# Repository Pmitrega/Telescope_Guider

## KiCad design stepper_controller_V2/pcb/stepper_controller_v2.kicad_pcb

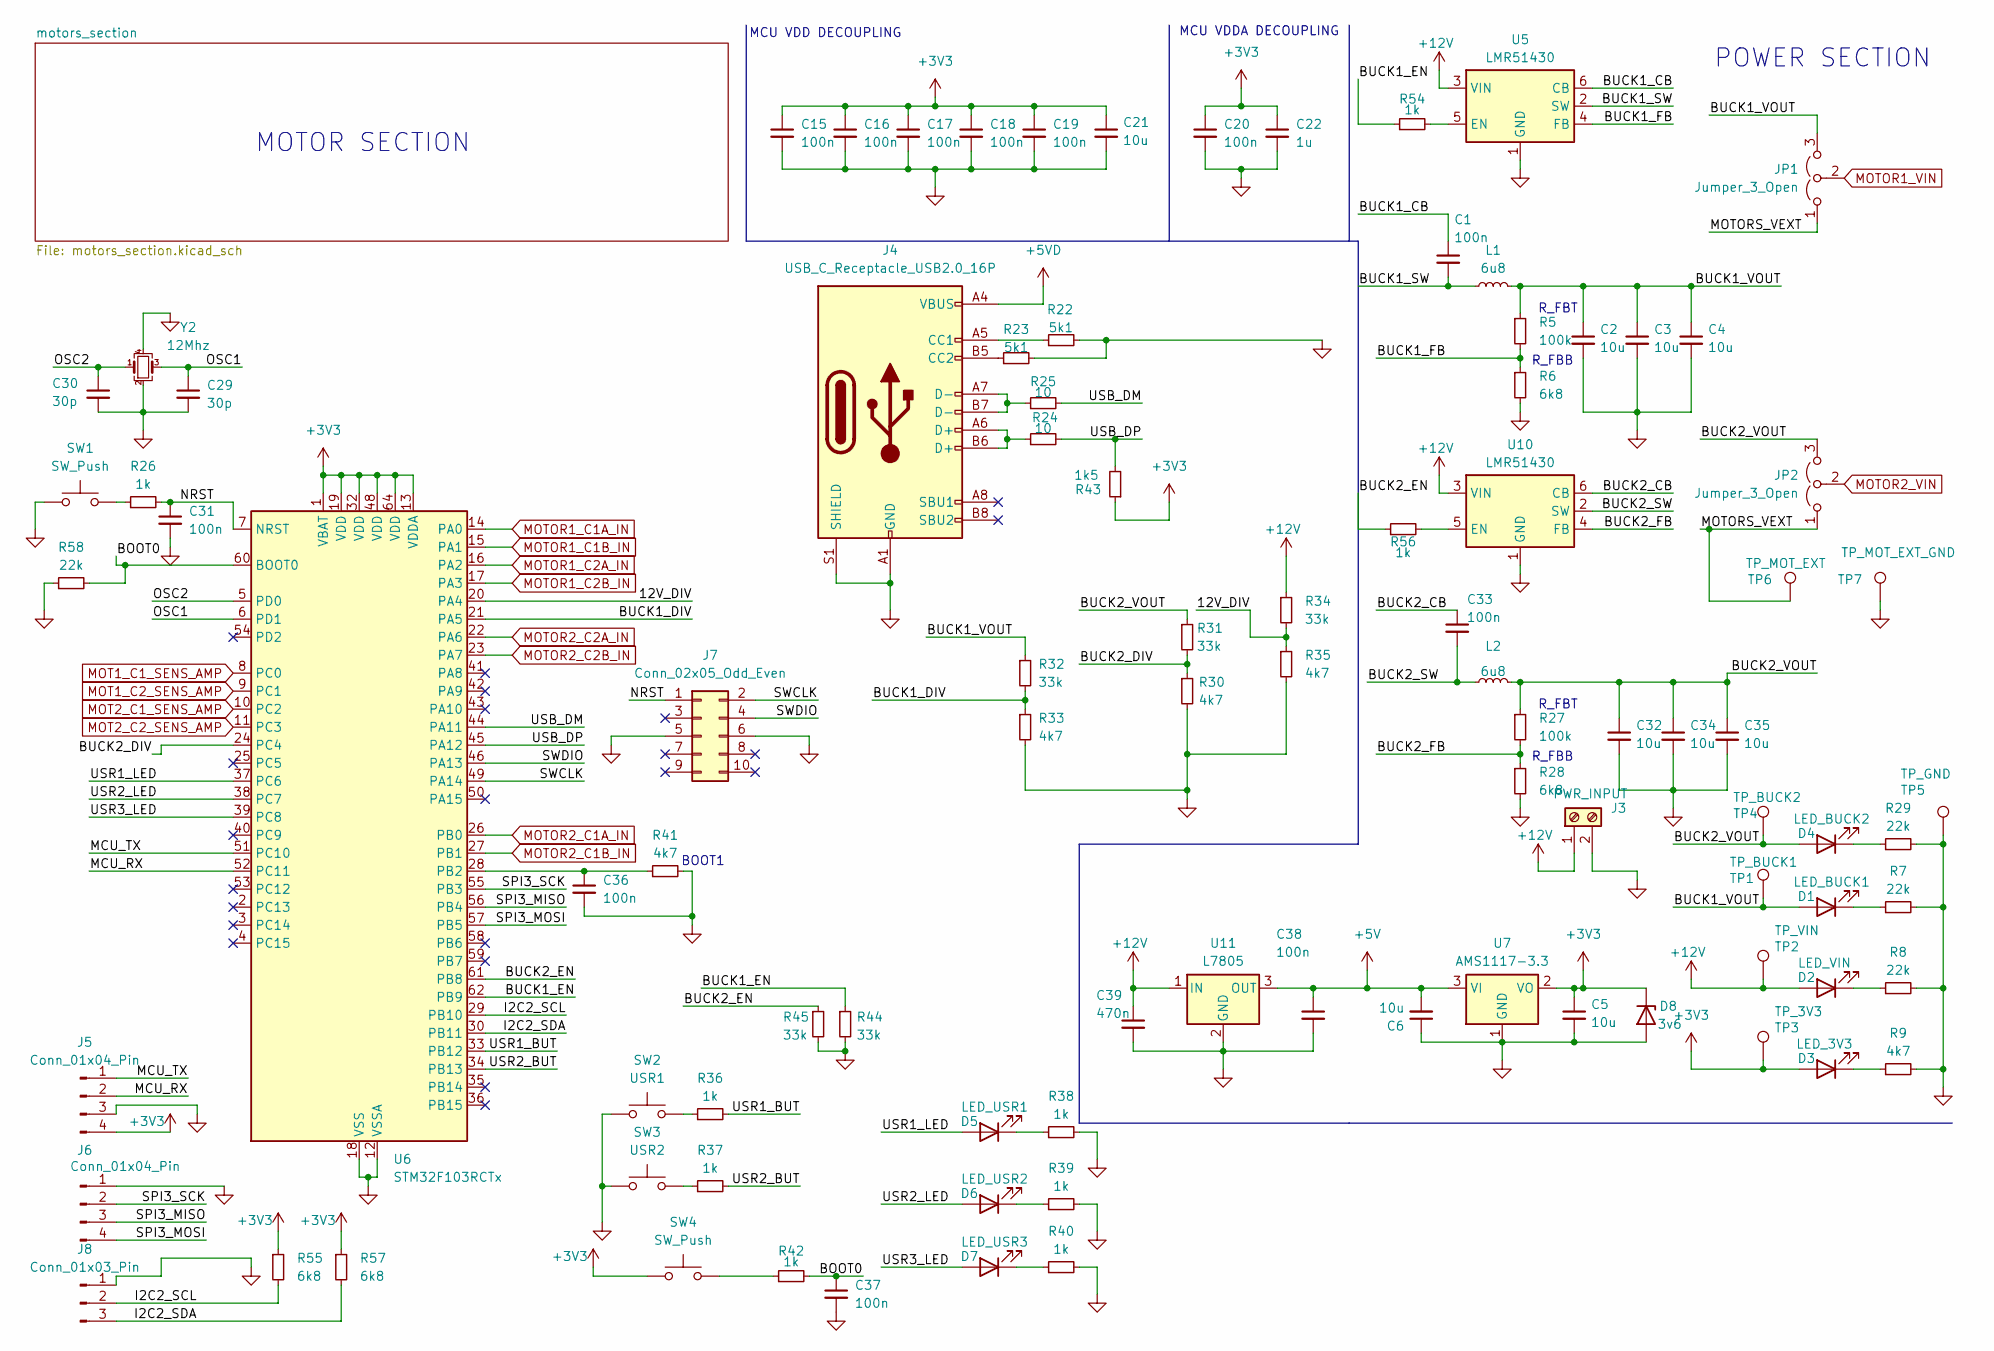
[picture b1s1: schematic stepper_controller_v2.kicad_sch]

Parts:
C1, C15, C16, C17, C18, C19, C20, C31, C33, C36, C37, C38: 100n; C_0603_1608Metric; LCSC C14663
C2, C3, C4, C5, C6, C21, C32, C34, C35: 10u; C_0805_2012Metric; LCSC C15850
C22: 1u; C_0603_1608Metric; LCSC C15849
C29, C30: 30p; C_0603_1608Metric; LCSC C1658
C39: 470n; C_0603_1608Metric; LCSC C1623
D1: LED_BUCK1; LED_0603_1608Metric; LCSC C2286
D2: LED_VIN; LED_0603_1608Metric; LCSC C2286
D3: LED_3V3; LED_0603_1608Metric; LCSC C2286
D4: LED_BUCK2; LED_0603_1608Metric; LCSC C2286
D5: LED_USR1; LED_0603_1608Metric; LCSC C2286
D6: LED_USR2; LED_0603_1608Metric; LCSC C2286
D7: LED_USR3; LED_0603_1608Metric; LCSC C2286
D8: 3v6; D_SOD-323; LCSC C12757
J3: PWR_INPUT; TerminalBlock_bornier-2_P5.08mm
J4: USB_C_Receptacle_USB2.0_16P; USB_C_Receptacle_GCT_USB4105-xx-A_16P_TopMnt_Horizontal; LCSC C2765186
J5, J6: Conn_01x04_Pin; PinHeader_1x04_P2.54mm_Vertical
J7: Conn_02x05_Odd_Even; IDC-Header_2x05_P2.54mm_Vertical
J8: Conn_01x03_Pin; PinHeader_1x03_P2.54mm_Vertical
JP1, JP2: Jumper_3_Open; SolderJumper-3_P1.3mm_Open_Pad1.0x1.5mm
L1, L2: 6u8; L_Changjiang_FNR8040S; LCSC C431374
R5, R27: 100k; R_0603_1608Metric; LCSC C25803
R6, R28, R55, R57: 6k8; R_0603_1608Metric; LCSC C23212
R7, R8, R29, R58: 22k; R_0603_1608Metric; LCSC C31850
R9, R30, R33, R35, R41: 4k7; R_0603_1608Metric; LCSC C23162
R22, R23: 5k1; R_0603_1608Metric; LCSC C23186
R24, R25: 10; R_0603_1608Metric; LCSC C22859
R26, R36, R37, R38, R39, R40, R42, R54, R56: 1k; R_0603_1608Metric; LCSC C21190
R31, R32, R34, R44, R45: 33k; R_0603_1608Metric; LCSC C4216
R43: 1k5; R_0603_1608Metric; LCSC C22843
SW1, SW4: SW_Push; stepper TACT_SWITCH; LCSC C720477
SW2: USR1; stepper TACT_SWITCH; LCSC C720477
SW3: USR2; stepper TACT_SWITCH; LCSC C720477
TP1: TP_BUCK1; TestPoint_Pad_D1.5mm
TP2: TP_VIN; TestPoint_Pad_D1.5mm
TP3: TP_3V3; TestPoint_Pad_D1.5mm
TP4: TP_BUCK2; TestPoint_Pad_D1.5mm
TP5: TP_GND; TestPoint_Pad_D1.5mm
TP6: TP_MOT_EXT; TestPoint_Pad_D1.5mm
TP7: TP_MOT_EXT_GND; TestPoint_Pad_D1.5mm
U5, U10: LMR51430; SOT-23-6; LCSC C5219261
U6: STM32F103RCTx; LQFP-64_10x10mm_P0.5mm; LCSC C8323
U7: AMS1117-3.3; SOT-223-3_TabPin2; LCSC C6186
U11: L7805; TO-252-2; LCSC C58069
Y2: 12Mhz; Crystal_SMD_3225-4Pin_3.2x2.5mm; LCSC C9002

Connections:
+3V3: C5.1, C15.1, C16.1, C17.1, C18.1, C19.1, C20.1, C21.1, C22.1, D3.2 (A), D8.1 (K), J5.4, R43.1, R55.1, R57.1, SW4.1, TP3.1, U6.1 (VBAT), U6.13 (VDDA), U6.19 (VDD), U6.32 (VDD), U6.48 (VDD), U6.64 (VDD), U7.2 (VO); also elsewhere on the board
+5V: C6.2, C38.1, U7.3 (VI), U11.3 (OUT)
+5VD: J4.A4 (VBUS), J4.A9 (VBUS), J4.B4 (VBUS), J4.B9 (VBUS)
+12V: C39.1, D2.2 (A), J3.1, R34.1, TP2.1, U5.3 (VIN), U10.3 (VIN), U11.1 (IN)
/12V_DIV: R34.2, R35.1, U6.20 (PA4)
/BOOT0: C37.1, R42.2, R58.2, U6.60 (BOOT0)
/BUCK1_CB: C1.1, U5.6 (CB)
/BUCK1_DIV: R32.2, R33.1, U6.21 (PA5)
/BUCK1_EN: R44.1, R54.1, U6.62 (PB9)
/BUCK1_FB: R5.2, R6.1, U5.4 (FB)
/BUCK1_SW: C1.2, L1.1, U5.2 (SW)
/BUCK1_VOUT: C2.1, C3.1, C4.1, D1.2 (A), JP1.3 (B), L1.2, R5.1, R32.1, TP1.1
/BUCK2_CB: C33.1, U10.6 (CB)
/BUCK2_DIV: R30.1, R31.2, U6.24 (PC4)
/BUCK2_EN: R45.1, R56.1, U6.61 (PB8)
/BUCK2_FB: R27.2, R28.1, U10.4 (FB)
/BUCK2_SW: C33.2, L2.1, U10.2 (SW)
/BUCK2_VOUT: C32.1, C34.1, C35.1, D4.2 (A), JP2.3 (B), L2.2, R27.1, R31.1, TP4.1
/I2C2_SCL: J8.2, R55.2, U6.29 (PB10)
/I2C2_SDA: J8.3, R57.2, U6.30 (PB11)
/MCU_RX: J5.2, U6.52 (PC11)
/MCU_TX: J5.1, U6.51 (PC10)
/MOTORS_VEXT: JP1.1 (A), JP2.1 (A), TP6.1
/NRST: C31.1, J7.1, R26.2, U6.7 (NRST)
/OSC1: C29.1, U6.6 (PD1), Y2.3
/OSC2: C30.1, U6.5 (PD0), Y2.1
/SPI3_MISO: J6.3, U6.56 (PB4)
/SPI3_MOSI: J6.4, U6.57 (PB5)
/SPI3_SCK: J6.2, U6.55 (PB3)
/SWCLK: J7.2, U6.49 (PA14)
/SWDIO: J7.4, U6.46 (PA13)
/USB_DM: R25.2, U6.44 (PA11)
/USB_DP: R24.2, R43.2, U6.45 (PA12)
/USR1_BUT: R36.2, U6.33 (PB12)
/USR1_LED: D5.2 (A), U6.37 (PC6)
/USR2_BUT: R37.2, U6.34 (PB13)
/USR2_LED: D6.2 (A), U6.38 (PC7)
/USR3_LED: D7.2 (A), U6.39 (PC8)
GND: C2.2, C3.2, C4.2, C5.2, C6.1, C15.2, C16.2, C17.2, C18.2, C19.2, C20.2, C21.2, C22.2, C29.2, C30.2, C31.2, C32.2, C34.2, C35.2, C36.2, C37.2, C38.2, C39.2, D8.2 (A), J3.2, J4.A1 (GND), J4.A12 (GND), J4.B1 (GND), J4.B12 (GND), J4.S1 (SHIELD), J5.3, J6.1, J7.5, J7.6, J8.1, R6.2, R7.2, R8.2, R9.2, R22.2, R23.2, R28.2, R29.2, R30.2, R33.2, R35.2, R38.2, R39.2, R40.2, R41.2, R44.2, R45.2, R58.1, SW1.1, SW2.1, SW3.1, TP5.1, TP7.1, U5.1 (GND), U6.12 (VSSA), U6.18 (VSS), U6.31 (VSS), U6.47 (VSS), U6.63 (VSS), U7.1 (GND), U10.1 (GND), U11.2 (GND), Y2.2, Y2.4; also elsewhere on the board
MOT1_C1_SENS_AMP: U6.8 (PC0); also elsewhere on the board
MOT1_C2_SENS_AMP: U6.9 (PC1); also elsewhere on the board
MOT2_C1_SENS_AMP: U6.10 (PC2); also elsewhere on the board
MOT2_C2_SENS_AMP: U6.11 (PC3); also elsewhere on the board
MOTOR1_C1A_IN: U6.14 (PA0); also elsewhere on the board
MOTOR1_C1B_IN: U6.15 (PA1); also elsewhere on the board
MOTOR1_C2A_IN: U6.16 (PA2); also elsewhere on the board
MOTOR1_C2B_IN: U6.17 (PA3); also elsewhere on the board
MOTOR1_VIN: JP1.2 (C); also elsewhere on the board
MOTOR2_C1A_IN: U6.26 (PB0); also elsewhere on the board
MOTOR2_C1B_IN: U6.27 (PB1); also elsewhere on the board
MOTOR2_C2A_IN: U6.22 (PA6); also elsewhere on the board
MOTOR2_C2B_IN: U6.23 (PA7); also elsewhere on the board
MOTOR2_VIN: JP2.2 (C); also elsewhere on the board
unnamed: D1.1 (K), R7.1
unnamed: D2.1 (K), R8.1
unnamed: D3.1 (K), R9.1
unnamed: D4.1 (K), R29.1
unnamed: D5.1 (K), R38.1
unnamed: D6.1 (K), R39.1
unnamed: D7.1 (K), R40.1
unnamed: J4.A5 (CC1), R22.1
unnamed: J4.B5 (CC2), R23.1
unnamed: J4.A6 (D+), J4.B6 (D+), R24.1
unnamed: J4.A7 (D-), J4.B7 (D-), R25.1
unnamed: R26.1, SW1.2
unnamed: R36.1, SW2.2
unnamed: R37.1, SW3.2
unnamed: R42.1, SW4.2
unnamed: R54.2, U5.5 (EN)
unnamed: C36.1, R41.1, U6.28 (PB2)
unnamed: R56.2, U10.5 (EN)

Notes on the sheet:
R_FBT
MOTOR SECTION
POWER SECTION
MCU VDD DECOUPLING
R_FBB
BOOT1
MCU VDDA DECOUPLING

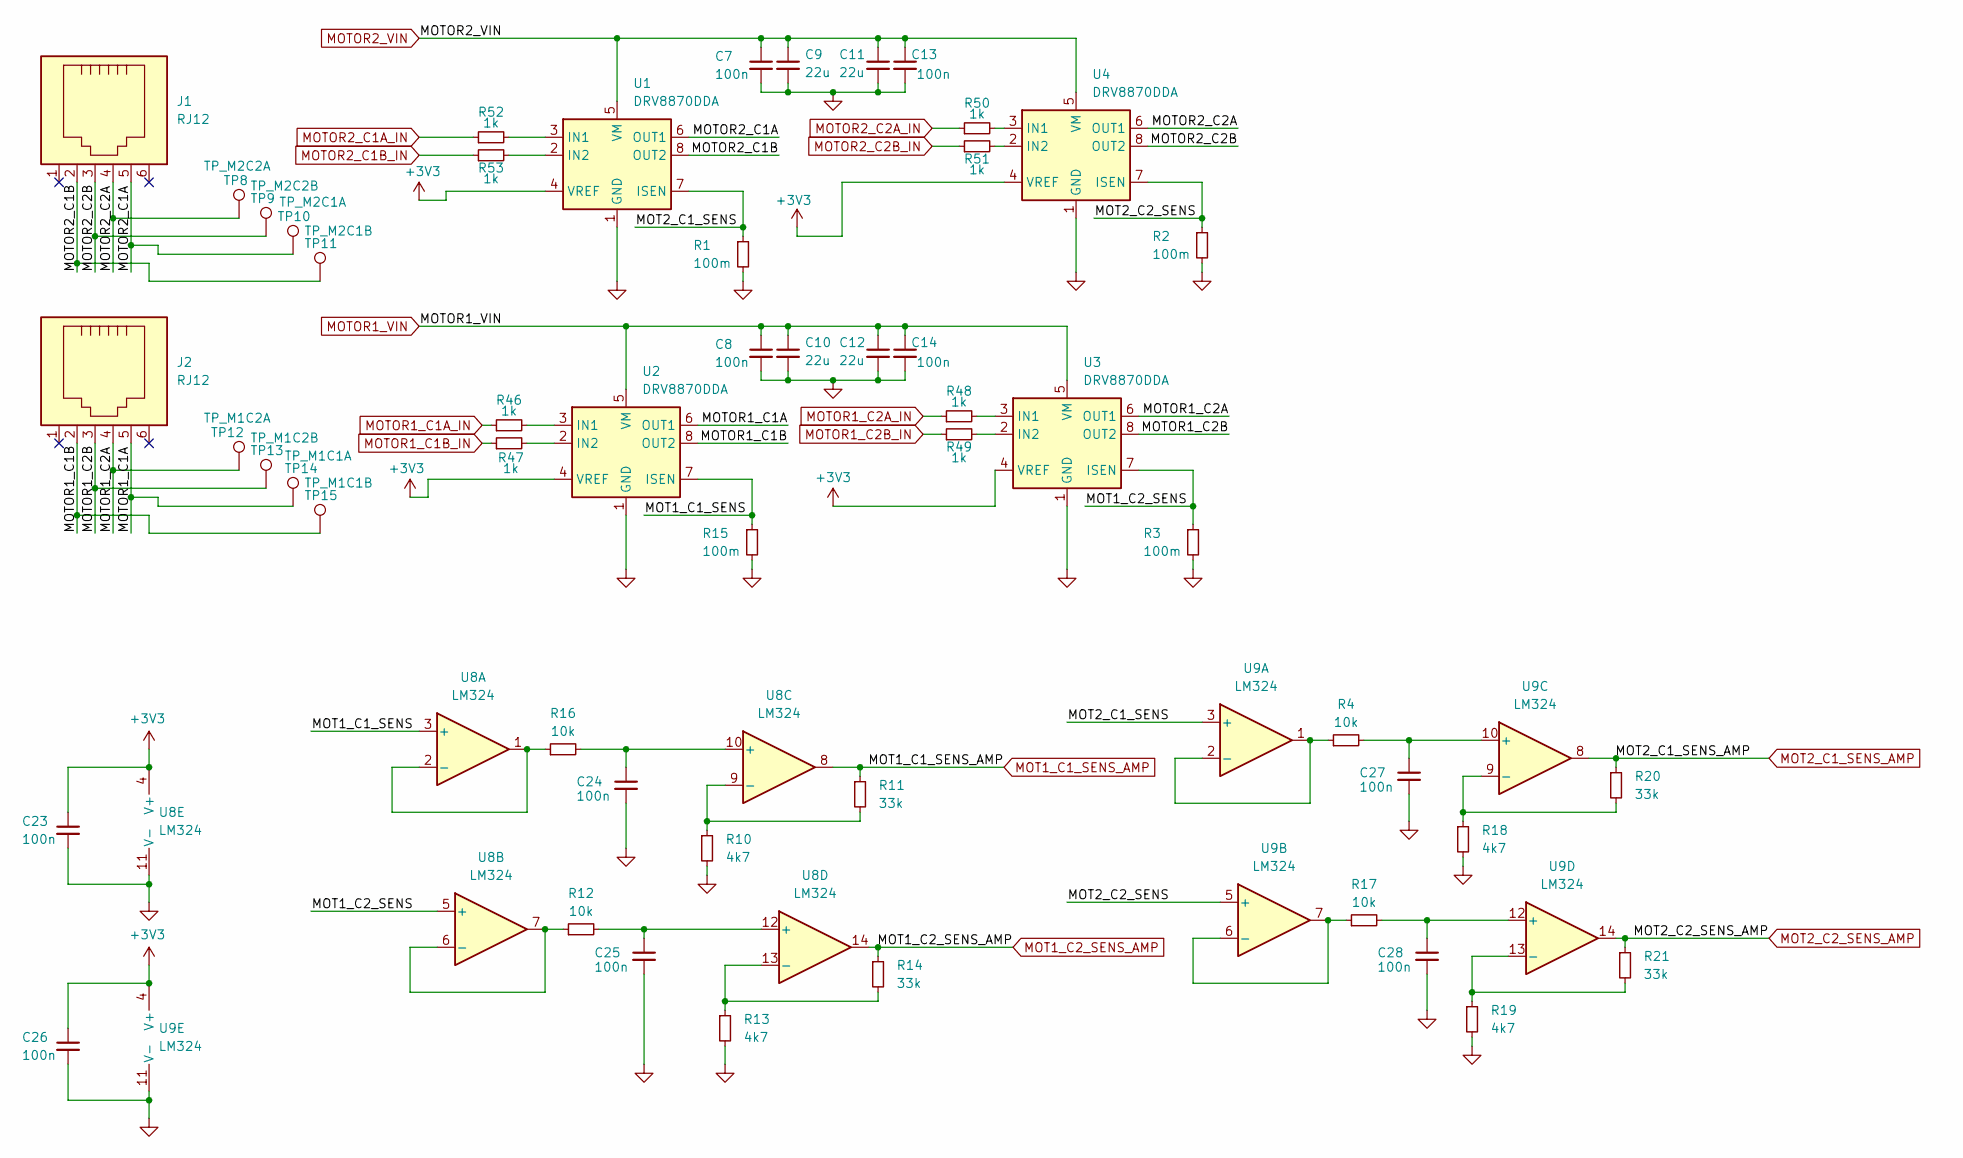
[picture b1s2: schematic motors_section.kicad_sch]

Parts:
C7, C8, C13, C14, C23, C24, C25, C26, C27, C28: 100n; C_0603_1608Metric; LCSC C14663
C9, C10, C11, C12: 22u; L_1210_3225Metric; LCSC C12891
J1, J2: RJ12; stepper ST4
R1, R2, R3, R15: 100m; R_0603_1608Metric; LCSC C111027
R4, R12, R16, R17: 10k; R_0603_1608Metric; LCSC C25804
R10, R13, R18, R19: 4k7; R_0603_1608Metric; LCSC C23162
R11, R14, R20, R21: 33k; R_0603_1608Metric; LCSC C4216
R46, R47, R48, R49, R50, R51, R52, R53: 1k; R_0603_1608Metric; LCSC C21190
TP8: TP_M2C2A; TestPoint_Pad_D1.0mm
TP9: TP_M2C2B; TestPoint_Pad_D1.0mm
TP10: TP_M2C1A; TestPoint_Pad_D1.0mm
TP11: TP_M2C1B; TestPoint_Pad_D1.0mm
TP12: TP_M1C2A; TestPoint_Pad_D1.0mm
TP13: TP_M1C2B; TestPoint_Pad_D1.0mm
TP14: TP_M1C1A; TestPoint_Pad_D1.0mm
TP15: TP_M1C1B; TestPoint_Pad_D1.0mm
U1, U2, U3, U4: DRV8870DDA; Texas_HTSOP-8-1EP_3.9x4.9mm_P1.27mm_EP2.95x4.9mm_Mask2.4x3.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; LCSC C86590
U8, U9: LM324; SOIC-14_3.9x8.7mm_P1.27mm; LCSC C71035

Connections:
+3V3: C23.1, C26.1, U1.4 (VREF), U2.4 (VREF), U3.4 (VREF), U4.4 (VREF), U8.4 (V+), U9.4 (V+); also elsewhere on the board
/motors_section/MOT1_C1_SENS: R15.1, U2.7 (ISEN), U8.3 (+)
/motors_section/MOT1_C2_SENS: R3.1, U3.7 (ISEN), U8.5 (+)
/motors_section/MOT2_C1_SENS: R1.1, U1.7 (ISEN), U9.3 (+)
/motors_section/MOT2_C2_SENS: R2.1, U4.7 (ISEN), U9.5 (+)
/motors_section/MOTOR1_C1A: J2.5, TP14.1, U2.6 (OUT1)
/motors_section/MOTOR1_C1B: J2.2, TP15.1, U2.8 (OUT2)
/motors_section/MOTOR1_C2A: J2.4, TP12.1, U3.6 (OUT1)
/motors_section/MOTOR1_C2B: J2.3, TP13.1, U3.8 (OUT2)
/motors_section/MOTOR2_C1A: J1.5, TP10.1, U1.6 (OUT1)
/motors_section/MOTOR2_C1B: J1.2, TP11.1, U1.8 (OUT2)
/motors_section/MOTOR2_C2A: J1.4, TP8.1, U4.6 (OUT1)
/motors_section/MOTOR2_C2B: J1.3, TP9.1, U4.8 (OUT2)
GND: C7.2, C8.2, C9.2, C10.2, C11.2, C12.2, C13.2, C14.2, C23.2, C24.2, C25.2, C26.2, C27.2, C28.2, R1.2, R2.2, R3.2, R10.2, R13.2, R15.2, R18.2, R19.2, U1.1 (GND), U1.9 (GND), U2.1 (GND), U2.9 (GND), U3.1 (GND), U3.9 (GND), U4.1 (GND), U4.9 (GND), U8.11 (V-), U9.11 (V-); also elsewhere on the board
MOT1_C1_SENS_AMP: R11.1, U8.8; also elsewhere on the board
MOT1_C2_SENS_AMP: R14.1, U8.14; also elsewhere on the board
MOT2_C1_SENS_AMP: R20.1, U9.8; also elsewhere on the board
MOT2_C2_SENS_AMP: R21.1, U9.14; also elsewhere on the board
MOTOR1_C1A_IN: R46.1; also elsewhere on the board
MOTOR1_C1B_IN: R47.1; also elsewhere on the board
MOTOR1_C2A_IN: R48.1; also elsewhere on the board
MOTOR1_C2B_IN: R49.1; also elsewhere on the board
MOTOR1_VIN: C8.1, C10.1, C12.1, C14.1, U2.5 (VM), U3.5 (VM); also elsewhere on the board
MOTOR2_C1A_IN: R52.1; also elsewhere on the board
MOTOR2_C1B_IN: R53.1; also elsewhere on the board
MOTOR2_C2A_IN: R50.1; also elsewhere on the board
MOTOR2_C2B_IN: R51.1; also elsewhere on the board
MOTOR2_VIN: C7.1, C9.1, C11.1, C13.1, U1.5 (VM), U4.5 (VM); also elsewhere on the board
unnamed: R52.2, U1.3 (IN1)
unnamed: R53.2, U1.2 (IN2)
unnamed: R46.2, U2.3 (IN1)
unnamed: R47.2, U2.2 (IN2)
unnamed: R48.2, U3.3 (IN1)
unnamed: R49.2, U3.2 (IN2)
unnamed: R50.2, U4.3 (IN1)
unnamed: R51.2, U4.2 (IN2)
unnamed: R16.1, U8.1, U8.2 (-)
unnamed: R12.1, U8.6 (-), U8.7
unnamed: C24.1, R16.2, U8.10 (+)
unnamed: R10.1, R11.2, U8.9 (-)
unnamed: C25.1, R12.2, U8.12 (+)
unnamed: R13.1, R14.2, U8.13 (-)
unnamed: R4.1, U9.1, U9.2 (-)
unnamed: R17.1, U9.6 (-), U9.7
unnamed: C27.1, R4.2, U9.10 (+)
unnamed: R18.1, R20.2, U9.9 (-)
unnamed: C28.1, R17.2, U9.12 (+)
unnamed: R19.1, R21.2, U9.13 (-)

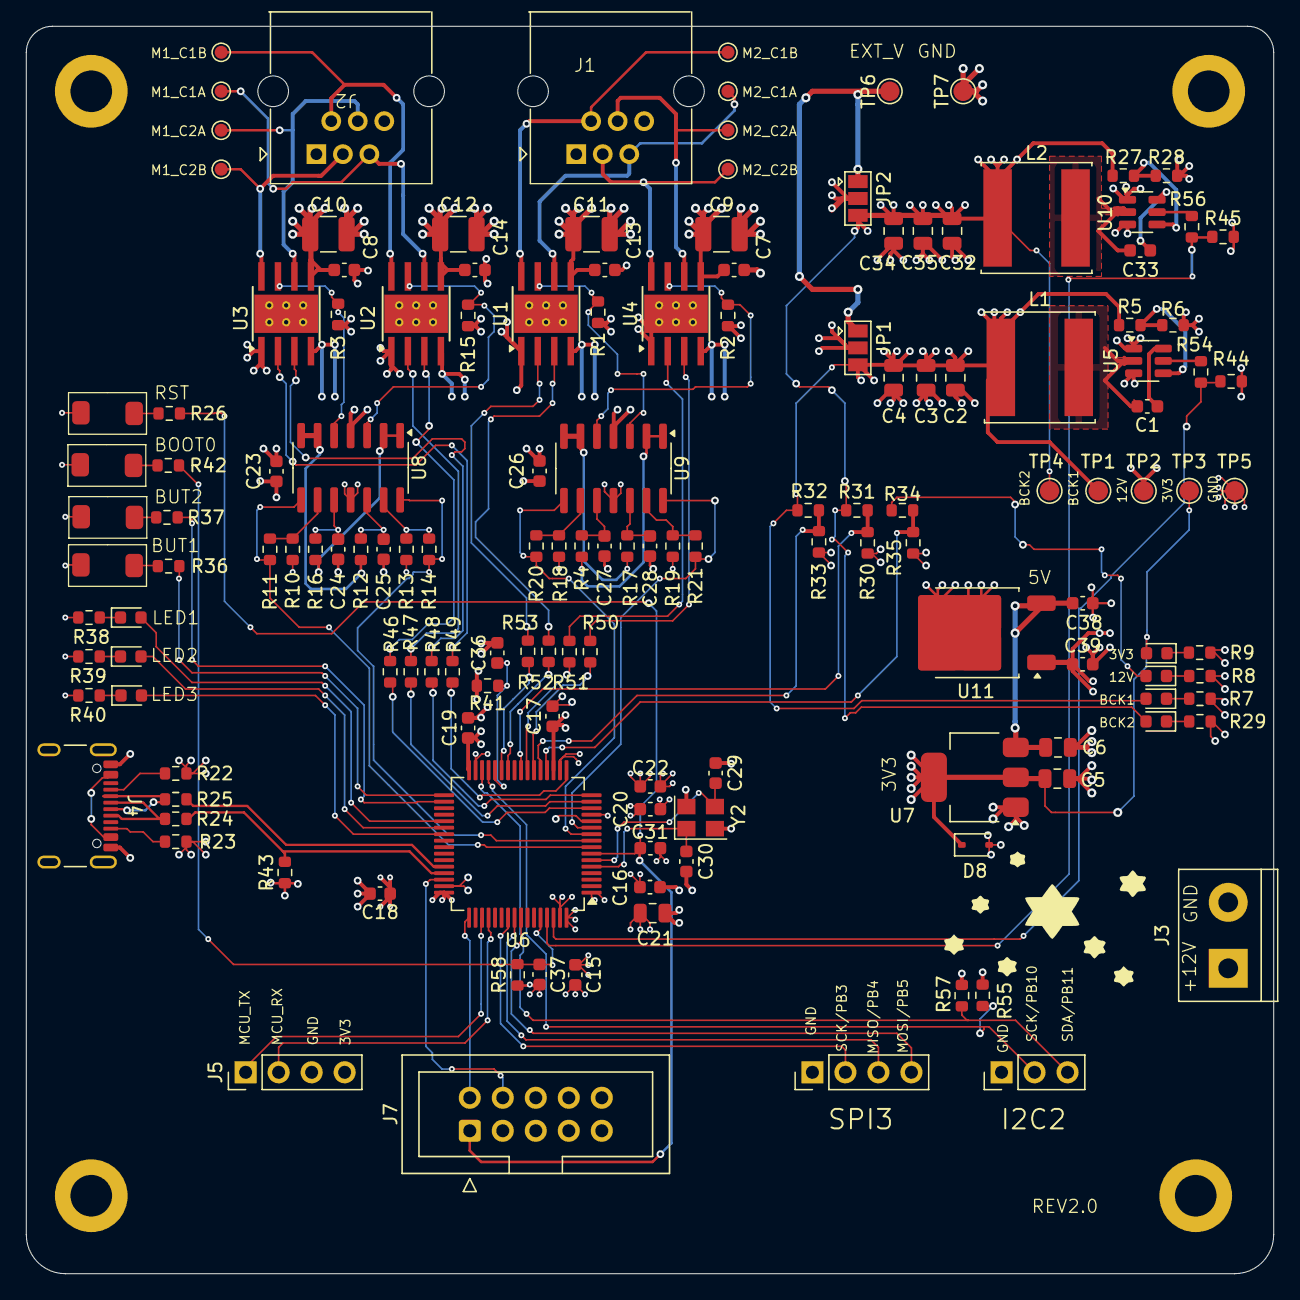
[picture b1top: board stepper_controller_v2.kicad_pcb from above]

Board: 4 copper layers, 96.0 x 96.0 mm, 148 parts (0 on the bottom side), 103 nets.

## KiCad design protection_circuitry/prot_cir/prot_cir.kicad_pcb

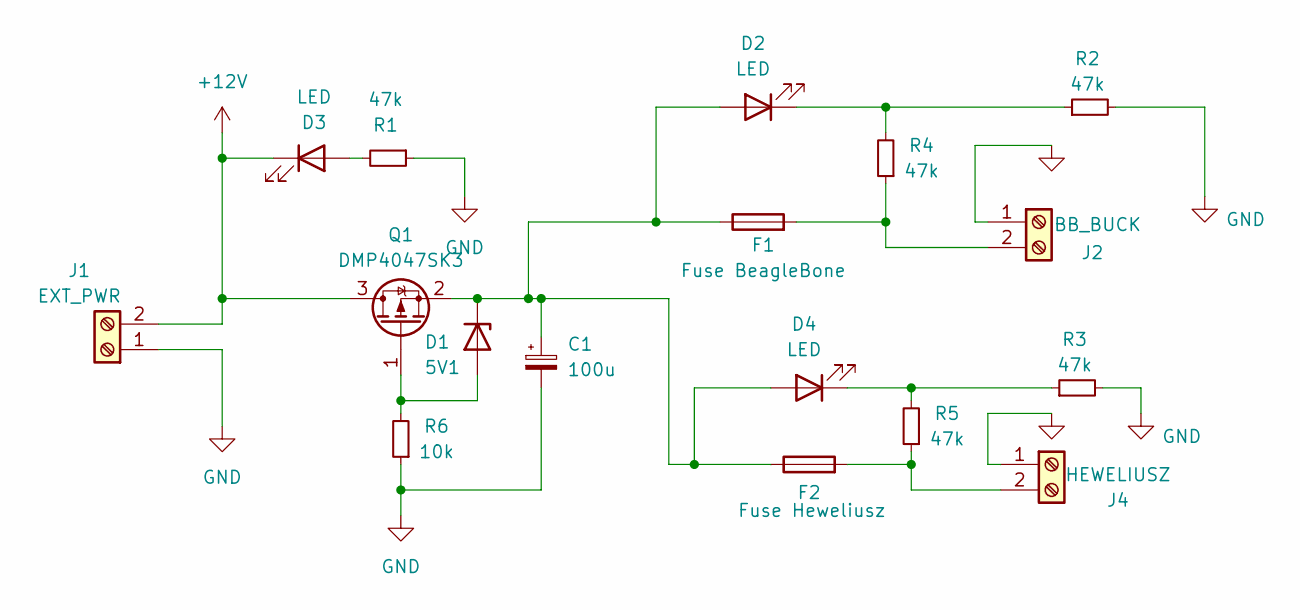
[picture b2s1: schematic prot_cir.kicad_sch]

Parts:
C1: 100u; CP_Radial_D6.3mm_P2.50mm
D1: 5V1; D_MiniMELF
D2, D3, D4: LED; LED_D3.0mm
F1: Fuse BeagleBone; Hewelusz_fuse_holder
F2: Fuse Heweliusz; Hewelusz_fuse_holder
J1: EXT_PWR; TerminalBlock_bornier-2_P5.08mm
J2: BB_BUCK; TerminalBlock_bornier-2_P5.08mm
J4: HEWELIUSZ; TerminalBlock_bornier-2_P5.08mm
Q1: DMP4047SK3; TO-252-2
R1, R2, R3, R4, R5: 47k; R_0603_1608Metric_Pad0.98x0.95mm_HandSolder
R6: 10k; R_0603_1608Metric_Pad0.98x0.95mm_HandSolder

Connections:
+12V: D3.1 (K), J1.2, Q1.3 (D)
GND: C1.2, J1.1, J2.1, J4.1, R1.1, R2.2, R3.2, R6.1
unnamed: D1.2 (A), Q1.1 (G), R6.2
unnamed: C1.1, D1.1 (K), D2.2 (A), D4.2 (A), F1.1, F2.1, Q1.2 (S)
unnamed: D2.1 (K), R2.1, R4.2
unnamed: D3.2 (A), R1.2
unnamed: D4.1 (K), R3.1, R5.2
unnamed: F1.2, J2.2, R4.1
unnamed: F2.2, J4.2, R5.1

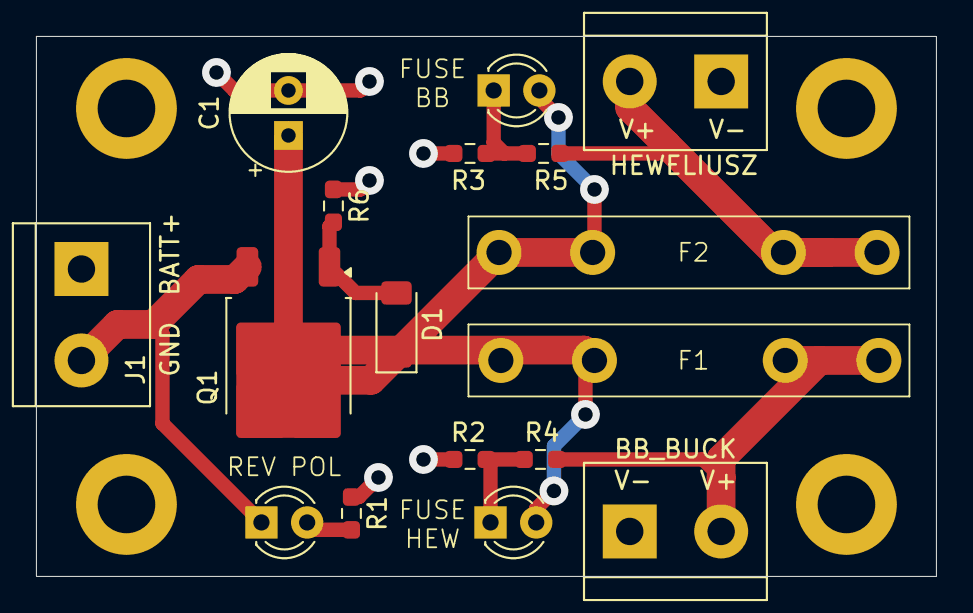
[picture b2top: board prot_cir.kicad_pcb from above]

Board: 2 copper layers, 50.0 x 30.0 mm, 17 parts (0 on the bottom side), 9 nets.

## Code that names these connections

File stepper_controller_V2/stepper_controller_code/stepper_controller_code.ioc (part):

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Mcu.Name=STM32F103R(C-D-E)Tx
Mcu.Package=LQFP64
Mcu.UserName=STM32F103RCTx
PA0-WKUP.Signal=S_TIM2_CH1_ETR
PA1.Signal=S_TIM2_CH2
PA11.Mode=Device
PA11.Signal=USB_DM
PA12.Mode=Device
PA12.Signal=USB_DP
PA13.Mode=Serial_Wire
PA13.Signal=SYS_JTMS-SWDIO
PA14.Mode=Serial_Wire
PA14.Signal=SYS_JTCK-SWCLK
PA2.Signal=S_TIM2_CH3
PA3.Signal=S_TIM2_CH4
PA4.Signal=ADCx_IN4
PA5.Signal=ADCx_IN5
PA6.Signal=S_TIM3_CH1
PA7.Signal=S_TIM3_CH2
PB0.Signal=S_TIM3_CH3
PB1.Signal=S_TIM3_CH4
PB10.Mode=I2C
PB10.Signal=I2C2_SCL
PB11.Mode=I2C
PB11.Signal=I2C2_SDA
PB12.GPIOParameters=GPIO_Label
PB12.GPIO_Label=USR1_BUT
PB12.Signal=GPIO_Input
PB13.GPIOParameters=GPIO_Label
PB13.GPIO_Label=USR2_BUT
PB13.Signal=GPIO_Input
PB5.GPIOParameters=GPIO_Label
PB5.GPIO_Label=BUZZER
PB5.Signal=GPIO_Output
PB8.GPIOParameters=GPIO_Label
PB8.GPIO_Label=BUCK2_EN
PB8.Signal=GPIO_Output
PB9.GPIOParameters=GPIO_Label
PB9.GPIO_Label=BUCK1_EN
PB9.Signal=GPIO_Output
PC0.Signal=ADCx_IN10
PC1.Signal=ADCx_IN11
PC10.Mode=Asynchronous
PC10.Signal=USART3_TX
PC11.Mode=Asynchronous
PC11.Signal=USART3_RX
PC2.Signal=ADCx_IN12
PC3.Signal=ADCx_IN13
PC4.Signal=ADCx_IN14
PC6.GPIOParameters=GPIO_Label
PC6.GPIO_Label=USR_LED1
PC6.Signal=S_TIM8_CH1
PC7.GPIOParameters=GPIO_Label
PC7.GPIO_Label=USR_LED2
PC7.Signal=S_TIM8_CH2
PC8.GPIOParameters=GPIO_Label
PC8.GPIO_Label=USR_LED3
PC8.Signal=S_TIM8_CH3
PD0-OSC_IN.Mode=HSE-External-Oscillator
PD0-OSC_IN.Signal=RCC_OSC_IN
PD1-OSC_OUT.Mode=HSE-External-Oscillator
PD1-OSC_OUT.Signal=RCC_OSC_OUT
RCC.HSE_VALUE=12000000
RCC.SYSCLKFreq_VALUE=72000000
RCC.SYSCLKSource=RCC_SYSCLKSOURCE_PLLCLK
board=custom

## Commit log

2024-07-04 adding code
2024-07-04 adding pcb
2024-08-17 code for Stepper controller - added battery monitoring, started creating motor driver
2024-08-17 updated pcb for second version - fixed issues with usb and filterin, added cascade ldo's
2024-09-11 Initialized imagerController
2024-09-19 added control for exposure and gain for ASI cameras
2024-09-21 added taking images for ASI camera
2024-09-27 added test file for starLocator
2024-09-27 Update main.cpp
    updated HELP info
2024-09-27 renamed helper program to proper name
2024-10-01 additional tests calculating centroid of star
2024-10-01 fixing problem on bb
2024-10-14 Added speed controll
2024-10-14 More precise speed control
2024-10-29 added .so for ASI camera and installation script
2024-10-29 Added searching best star and matching algorithm
2024-10-29 added telescope identifier module
2024-11-01 adding better cmd control
2024-11-03 added resistance aproxi
2024-11-03 added GUI
2024-11-06 adding web proxy
2024-11-06 added stepper Comm module
2024-11-07 added comm module to stepper
2024-11-11 added mqtt client
2024-11-13 added buzzer handling
2024-11-14 updated stepper comm
2024-11-14 created mqtt client
2024-11-14 updated gui
2024-11-14 update cmake
2024-11-14 added test with streaming camera
2024-11-14 updated tests with publishing sensors info
2024-11-14 GUI update
2024-11-15 added libs for camera
2024-11-15 updating install script
2024-11-17 install script
2024-11-17 "Added controll over network and created separate threads for different jobs"
2024-11-17 update for gui related for guider changes
2024-11-17 updated stepper controller with power manager
2024-11-18 fixing bug
2024-11-24 Update instructions
2024-11-25 added ASI lib for 64 linux
2024-11-25 star following algo
2024-11-25 motor resistance estimaton
2024-11-26 adding boost lib to repo
2024-11-26 Removing c++20 dependency
2024-11-26 loop for checking status
2024-11-26 added cammera disconnection handler and video capture
2024-11-26 lowering P2P voltage of motor to reduce it's heating
2024-11-27 added compression
2024-11-27 added compressed image handling
2024-11-28 added image transformation for preview
2024-11-30 adding led images
2024-12-01 web server and binarization
2024-12-03 solverServer
2024-12-10 added astrometry solver server
2024-12-10 updated worker to handle interval time
2024-12-10 adding motors enabling/disabling
2024-12-10 added support for motors shutdown
2024-12-10 added interval info for mqtt
2024-12-10 fixing bug with one coil on wafter shutdown
2024-12-12 added motors coil monitoring
2024-12-12 added kalman
2024-12-14 update of solver server for differnet sensor size
2024-12-15 Updating gui, added not working kalman :D
2024-12-15 Added control by number of steps
2024-12-18 adding new, better GUI
2024-12-19 Update GUI
2024-12-26 made some changes to GUI, resolved issue that motors was not stoping after identification
2024-12-26 Now image buffer is read countinously so there is no lag when interval is greater than exposure
2025-01-18 Create schemes folder
2025-01-18 Dodano PowerManager.drawio
2025-01-18 Dodano buzzer.drawio
2025-01-20 fixed sending issue
2025-01-20 added resistance sending
2025-02-26 added sqrt preview, logger
2025-02-28 added COG star center finding method, logoing of set point and error values
2025-03-22 added kabsch
2025-04-01 added image straeamer
2025-04-11 Update GUI, with resizing and test modes
2025-04-11 fixed spaces in sovleServer, added test images streaming
2025-04-11 added correction for center from WCS
2025-04-11 added whole WCS information
2025-04-14 updated with corrected WCS
2025-04-14 Update GUI, added grid, corrections to WCS
2025-04-20 addes star detection lagorithms an controllers
2025-04-23 moving grid
2025-04-24 adding motor position monitoring
2025-04-24 adding motor position monitoring fix
2025-04-25 fiexd moniotring
2025-04-25 series 3 images
2025-04-25 update for monitoring star greenwitch hr
2025-04-27 change for fp
2025-06-19 Grande finale
2025-07-14 Dodano dsdsadsadsadsadsa.drawio
